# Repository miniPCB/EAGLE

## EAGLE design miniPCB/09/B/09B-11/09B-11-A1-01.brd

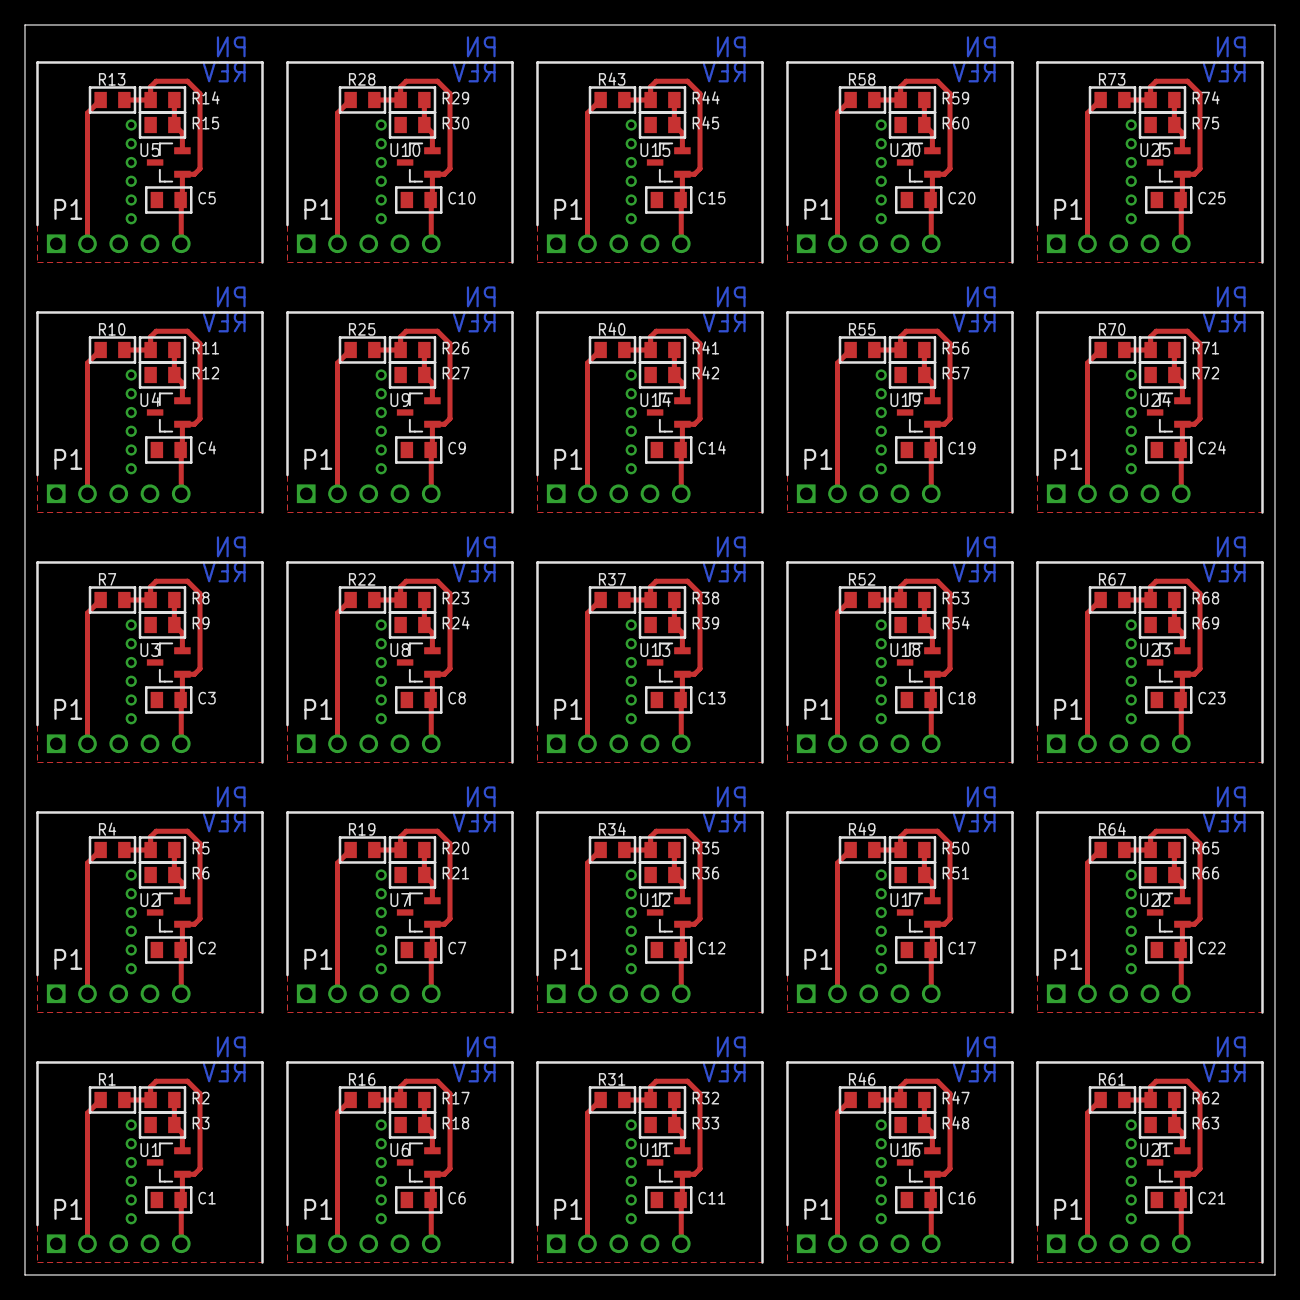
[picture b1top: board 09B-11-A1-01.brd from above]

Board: 2 copper layers, 100.0 x 100.0 mm, 175 parts (0 on the bottom side), 100 nets.

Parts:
C1, C2, C3, C4, C5, C6, C7, C8, C9, C10, C11, C12, C13, C14, C15, C16, C17, C18, C19, C20, C21, C22, C23, C24, C25: C0805
P1, P2, P3, P4, P5, P6, P7, P8, P9, P10, P11, P12, P13, P14, P15, P16, P17, P18, P19, P20, P21, P22, P23, P24, P25: PINS_1X5
PCB1, PCB2, PCB3, PCB4, PCB5, PCB6, PCB7, PCB8, PCB9, PCB10, PCB11, PCB12, PCB13, PCB14, PCB15, PCB16, PCB17, PCB18, PCB19, PCB20, PCB21, PCB22, PCB23, PCB24, PCB25: PCB20-20
R1, R2, R3, R4, R5, R6, R7, R8, R9, R10, R11, R12, R13, R14, R15, R16, R17, R18, R19, R20, R21, R22, R23, R24, R25, R26, R27, R28, R29, R30, R31, R32, R33, R34, R35, R36, R37, R38, R39, R40, R41, R42, R43, R44, R45, R46, R47, R48, R49, R50, R51, R52, R53, R54, R55, R56, R57, R58, R59, R60, R61, R62, R63, R64, R65, R66, R67, R68, R69, R70, R71, R72, R73, R74, R75: R0805
U1, U2, U3, U4, U5, U6, U7, U8, U9, U10, U11, U12, U13, U14, U15, U16, U17, U18, U19, U20, U21, U22, U23, U24, U25: TL432BQDBZRQ1; SOT95P237X112-3N

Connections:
GND20: C1.2ASDF, P1.1, R3.1, U1.3
GND21: C2.2ASDF, P2.1, R6.1, U2.3
GND22: C3.2ASDF, P3.1, R9.1, U3.3
GND23: C4.2ASDF, P4.1, R12.1, U4.3
GND24: C5.2ASDF, P5.1, R15.1, U5.3
GND25: C6.2ASDF, P6.1, R18.1, U6.3
GND26: C7.2ASDF, P7.1, R21.1, U7.3
GND27: C8.2ASDF, P8.1, R24.1, U8.3
GND28: C9.2ASDF, P9.1, R27.1, U9.3
GND29: C10.2ASDF, P10.1, R30.1, U10.3
GND30: C11.2ASDF, P11.1, R33.1, U11.3
GND31: C12.2ASDF, P12.1, R36.1, U12.3
GND32: C13.2ASDF, P13.1, R39.1, U13.3
GND33: C14.2ASDF, P14.1, R42.1, U14.3
GND34: C15.2ASDF, P15.1, R45.1, U15.3
GND35: C16.2ASDF, P16.1, R48.1, U16.3
GND36: C17.2ASDF, P17.1, R51.1, U17.3
GND37: C18.2ASDF, P18.1, R54.1, U18.3
GND38: C19.2ASDF, P19.1, R57.1, U19.3
GND39: C20.2ASDF, P20.1, R60.1, U20.3
GND40: C21.2ASDF, P21.1, R63.1, U21.3
GND41: C22.2ASDF, P22.1, R66.1, U22.3
GND42: C23.2ASDF, P23.1, R69.1, U23.3
GND43: C24.2ASDF, P24.1, R72.1, U24.3
GND44: C25.2ASDF, P25.1, R75.1, U25.3
unnamed: C1.1ASD, P1.5, R1.1, R2.2, U1.1
unnamed: R2.1, R3.2, U1.2
unnamed: C2.1ASD, P2.5, R4.1, R5.2, U2.1
unnamed: R5.1, R6.2, U2.2
unnamed: C3.1ASD, P3.5, R7.1, R8.2, U3.1
unnamed: R8.1, R9.2, U3.2
unnamed: C4.1ASD, P4.5, R10.1, R11.2, U4.1
unnamed: R11.1, R12.2, U4.2
unnamed: C5.1ASD, P5.5, R13.1, R14.2, U5.1
unnamed: R14.1, R15.2, U5.2
unnamed: C6.1ASD, P6.5, R16.1, R17.2, U6.1
unnamed: R17.1, R18.2, U6.2
unnamed: C7.1ASD, P7.5, R19.1, R20.2, U7.1
unnamed: R20.1, R21.2, U7.2
unnamed: C8.1ASD, P8.5, R22.1, R23.2, U8.1
unnamed: R23.1, R24.2, U8.2
unnamed: C9.1ASD, P9.5, R25.1, R26.2, U9.1
unnamed: R26.1, R27.2, U9.2
unnamed: C10.1ASD, P10.5, R28.1, R29.2, U10.1
unnamed: R29.1, R30.2, U10.2
unnamed: C11.1ASD, P11.5, R31.1, R32.2, U11.1
unnamed: R32.1, R33.2, U11.2
unnamed: C12.1ASD, P12.5, R34.1, R35.2, U12.1
unnamed: R35.1, R36.2, U12.2
unnamed: C13.1ASD, P13.5, R37.1, R38.2, U13.1
unnamed: R38.1, R39.2, U13.2
unnamed: C14.1ASD, P14.5, R40.1, R41.2, U14.1
unnamed: R41.1, R42.2, U14.2
unnamed: C15.1ASD, P15.5, R43.1, R44.2, U15.1
unnamed: R44.1, R45.2, U15.2
unnamed: C16.1ASD, P16.5, R46.1, R47.2, U16.1
unnamed: R47.1, R48.2, U16.2
unnamed: C17.1ASD, P17.5, R49.1, R50.2, U17.1
unnamed: R50.1, R51.2, U17.2
unnamed: C18.1ASD, P18.5, R52.1, R53.2, U18.1
unnamed: R53.1, R54.2, U18.2
unnamed: C19.1ASD, P19.5, R55.1, R56.2, U19.1
unnamed: R56.1, R57.2, U19.2
unnamed: C20.1ASD, P20.5, R58.1, R59.2, U20.1
unnamed: R59.1, R60.2, U20.2
unnamed: C21.1ASD, P21.5, R61.1, R62.2, U21.1
unnamed: R62.1, R63.2, U21.2
unnamed: C22.1ASD, P22.5, R64.1, R65.2, U22.1
unnamed: R65.1, R66.2, U22.2
unnamed: C23.1ASD, P23.5, R67.1, R68.2, U23.1
unnamed: R68.1, R69.2, U23.2
unnamed: C24.1ASD, P24.5, R70.1, R71.2, U24.1
unnamed: R71.1, R72.2, U24.2
unnamed: C25.1ASD, P25.5, R73.1, R74.2, U25.1
unnamed: R74.1, R75.2, U25.2
V+: P1.2, R1.2
V+1: P2.2, R4.2
V+2: P3.2, R7.2
V+3: P4.2, R10.2
V+4: P5.2, R13.2
V+5: P6.2, R16.2
V+6: P7.2, R19.2
V+7: P8.2, R22.2
V+8: P9.2, R25.2
V+9: P10.2, R28.2
V+10: P11.2, R31.2
V+11: P12.2, R34.2
V+12: P13.2, R37.2
V+13: P14.2, R40.2
V+14: P15.2, R43.2
V+15: P16.2, R46.2
V+16: P17.2, R49.2
V+17: P18.2, R52.2
V+18: P19.2, R55.2
V+19: P20.2, R58.2
V+20: P21.2, R61.2
V+21: P22.2, R64.2
V+22: P23.2, R67.2
V+23: P24.2, R70.2
V+24: P25.2, R73.2

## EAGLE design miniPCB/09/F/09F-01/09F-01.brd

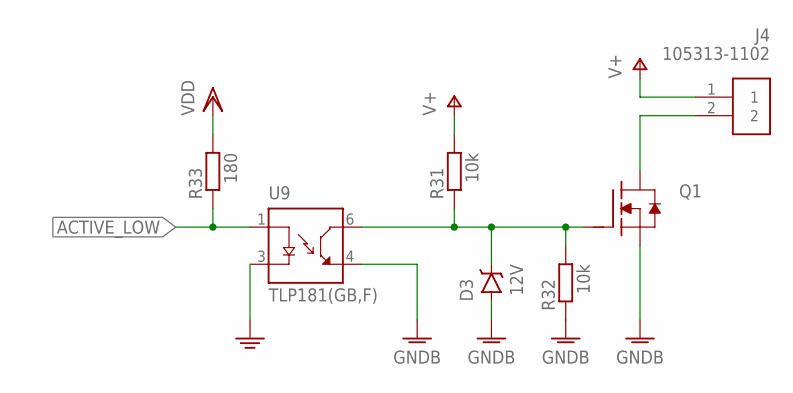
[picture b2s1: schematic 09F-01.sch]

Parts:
D3: 12V; SOT23
J4: 105313-1102; PINS_2-NANOFIT-H
Q1: MOSFET-NDPAK; DPACK
R31, R32: 10k; R0805
R33: 180; R0805
U9: TLP181(GB,F); SOIC254P700X280-4N

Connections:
ACTIVE_LOW: R33.1, U9.1 (A)
GND: U9.3 (C)
GNDB: D3.1 (A), Q1.3 (S), R32.1, U9.4 (ET)
unnamed: D3.3 (C), Q1.1 (G), R31.1, R32.2, U9.6 (CT)
unnamed: J4.2, Q1.4 (D)
V+: J4.1, R31.2
VDD: R33.2

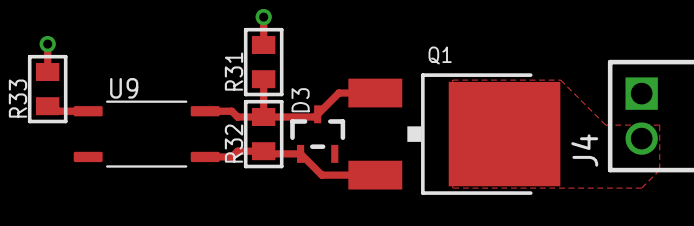
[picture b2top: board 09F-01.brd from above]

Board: 2 copper layers, 7 parts (0 on the bottom side), 5 nets.

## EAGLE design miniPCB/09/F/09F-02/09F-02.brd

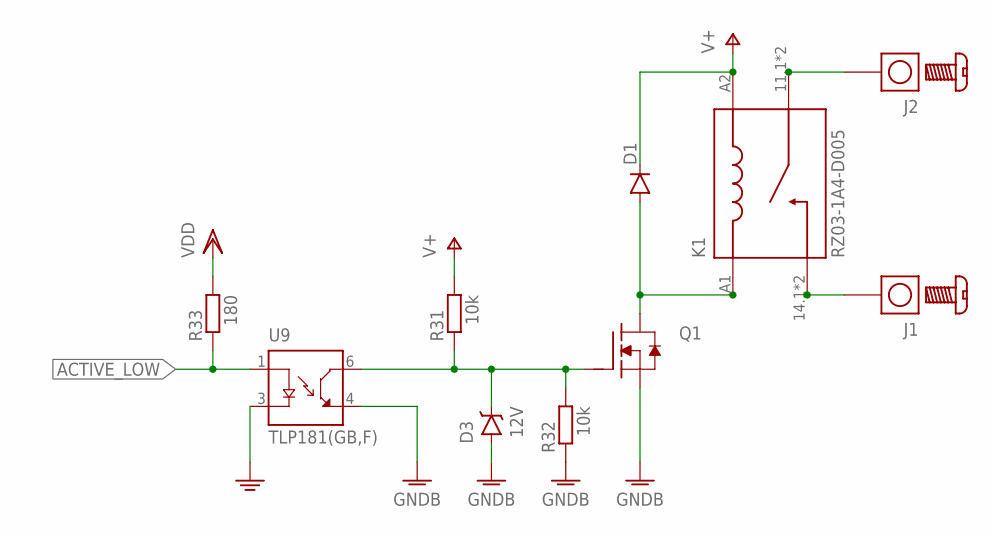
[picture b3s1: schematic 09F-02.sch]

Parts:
D1: DIODE-SOD323-W; SOD323-W
D3: 12V; SOT23
J1, J2: SCREW-TERMINAL; SCREW-TERMINAL-M3
K1: RZ03-1A4-D005; RELAY_RZ03-1A4-D005
Q1: MOSFET-NSOT23; SOT23
R31, R32: 10k; R0805
R33: 180; R0805
U9: TLP181(GB,F); SOIC254P700X280-4N

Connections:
ACTIVE_LOW: R33.1, U9.1 (A)
GND: U9.3 (C)
GNDB: D3.1 (A), Q1.2 (S), R32.1, U9.4 (ET)
unnamed: J2.1, J2.2, J2.3, J2.4, K1.11.1 (11), K1.11.2 (11)
unnamed: J1.1, J1.2, J1.3, J1.4, K1.14.1 (14), K1.14.2 (14)
unnamed: D3.3 (C), Q1.1 (G), R31.1, R32.2, U9.6 (CT)
unnamed: D1.A, K1.A1, Q1.3 (D)
V+: D1.C, K1.A2, R31.2
VDD: R33.2

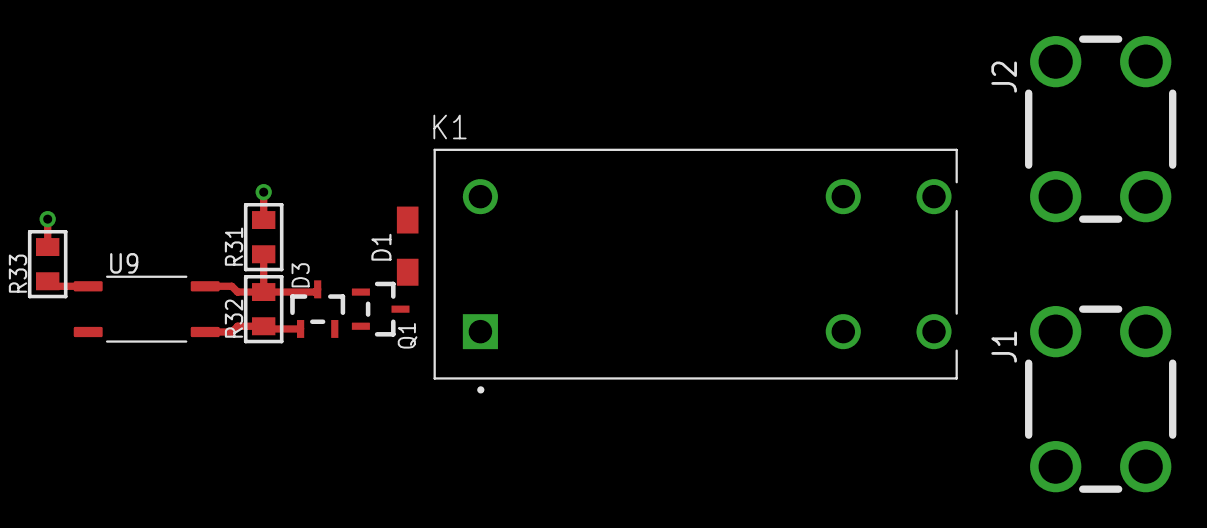
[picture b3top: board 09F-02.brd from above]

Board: 2 copper layers, 10 parts (0 on the bottom side), 7 nets.

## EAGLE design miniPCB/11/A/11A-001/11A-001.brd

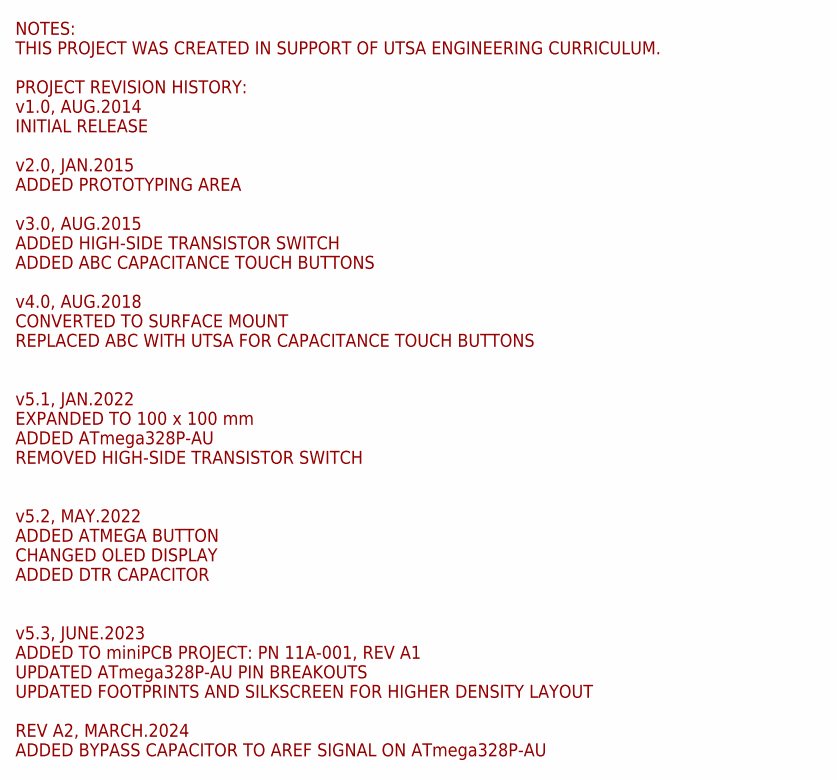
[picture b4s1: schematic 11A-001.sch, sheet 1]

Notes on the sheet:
NOTES: THIS PROJECT WAS CREATED IN SUPPORT OF UTSA ENGINEERING CURRICULUM. PROJECT REVISION HISTORY: v1.0, AUG.2014 INITIAL RELEASE v2.0, JAN.2015 ADDED PROTOTYPING AREA v3.0, AUG.2015 ADDED HIGH-SIDE TRANSISTOR SWITCH ADDED ABC CAPACITANCE TOUCH BUTTONS v4.0, AUG.2018 CONVERTED TO SURFACE MOUNT RE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

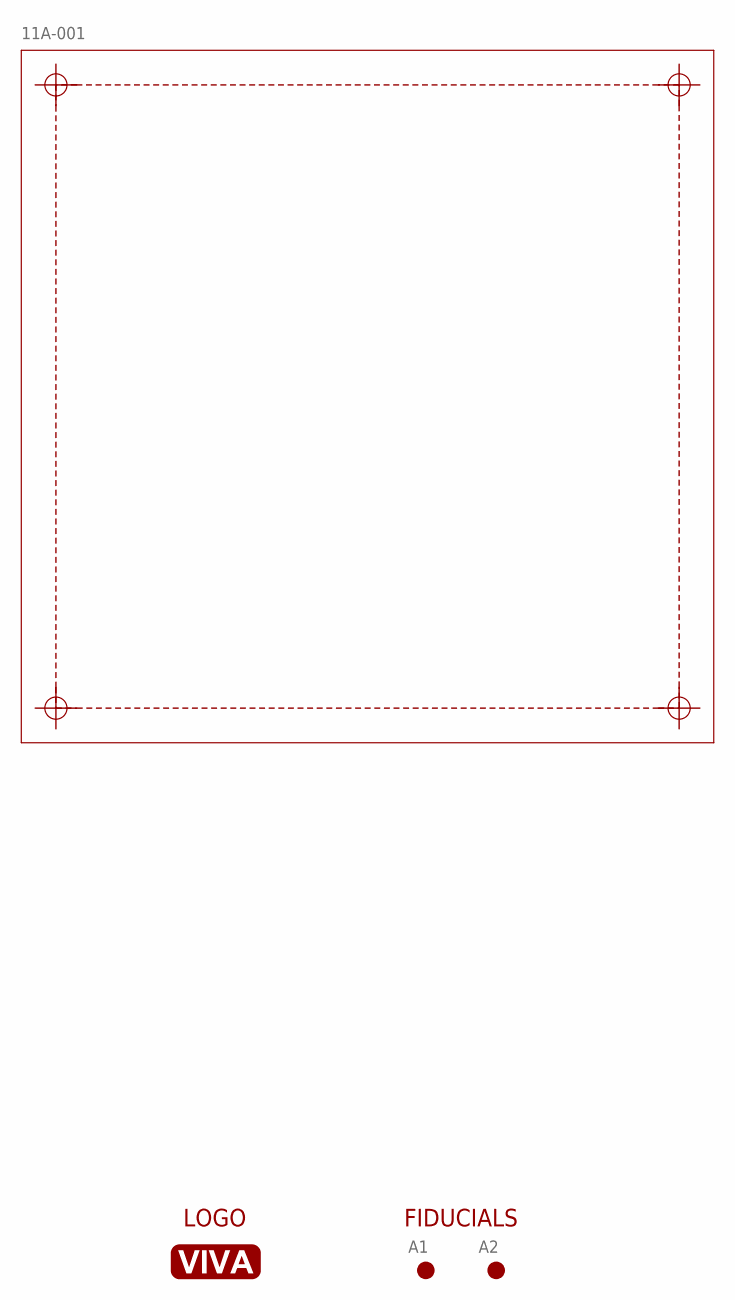
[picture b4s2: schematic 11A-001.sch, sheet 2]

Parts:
-: 11A-001; PCB_100X100
A1, A2: FIDUCIAL
U$2: VIVA_LOGO

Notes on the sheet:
FIDUCIALS
LOGO

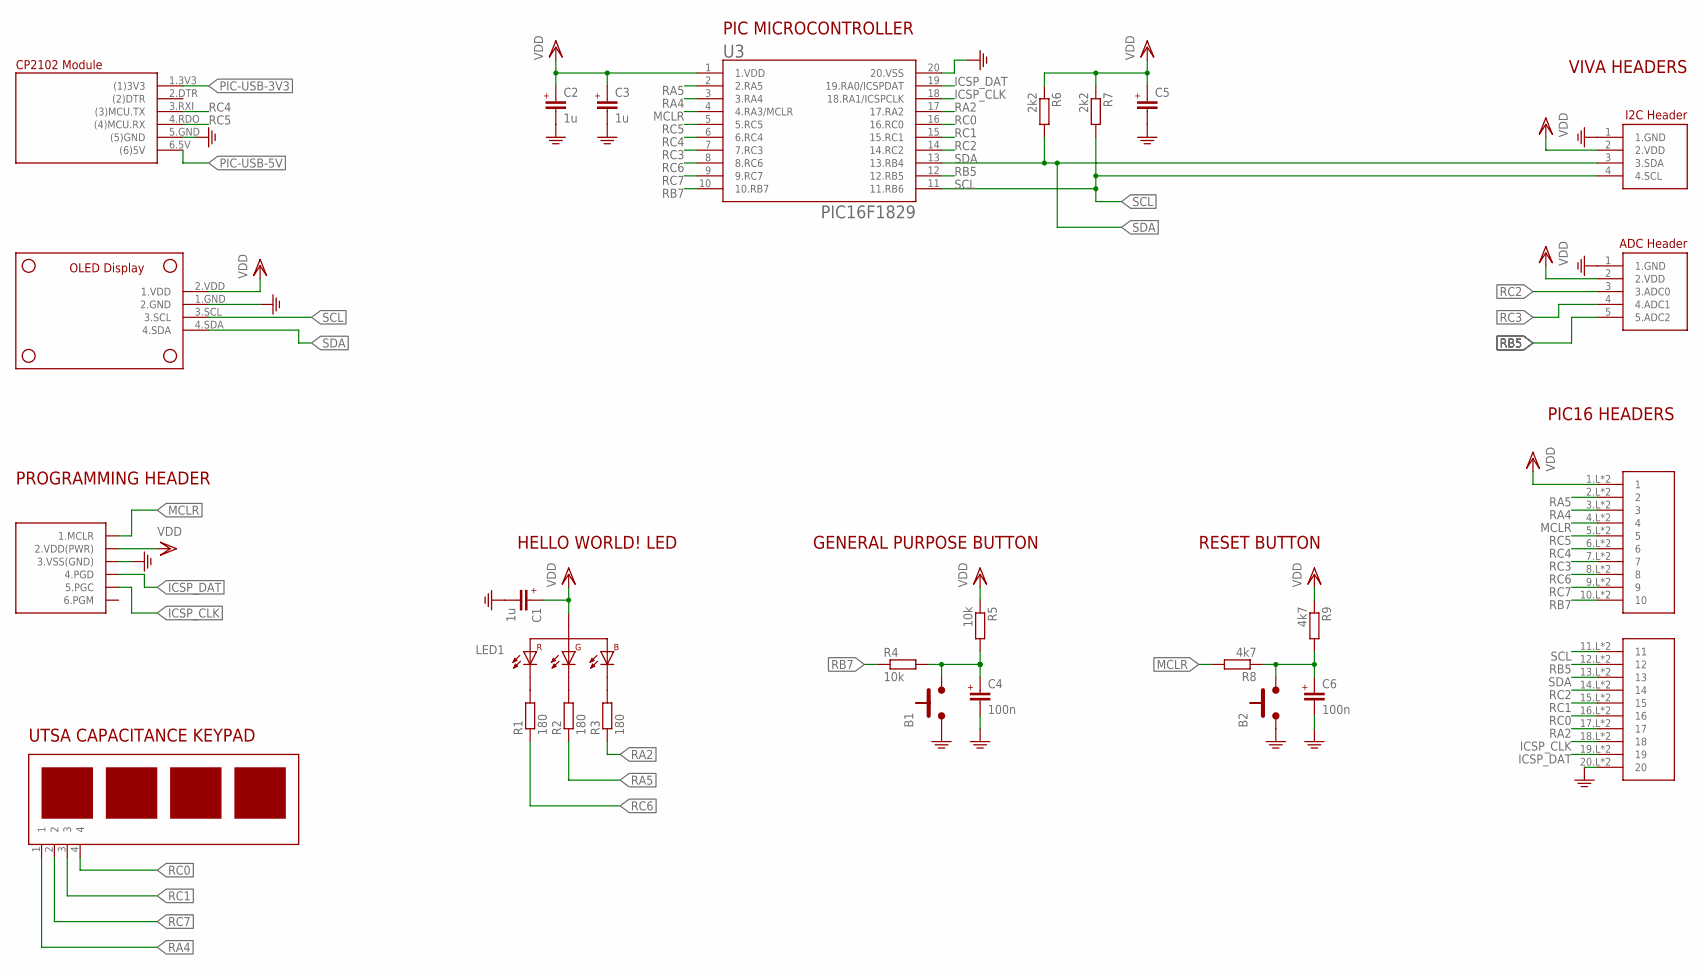
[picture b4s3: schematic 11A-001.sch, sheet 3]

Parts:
$3_73_$: VIVA_OLEDGND; VIVA_OLED-I2C-ALT
B1, B2: PUSHBUTTON6X6MM; 6X6MM
C1, C2, C3: 1u; C0805
C4, C6: 100n; C0805
C5: C0805
J1: PICKIT3
J2: VIVA-HEADER-ADC-PIC16
LED1: LED_RGBLTST-C19FD1WT; 0805_RGB
R1, R2, R3: 180; R0805
R4, R5: 10k; R0805
R6, R7: 2k2; R0805
R8, R9: 4k7; R0805
U1: VIVA_UTSA-KEYPADV5; VIVA_UTSA-KEYPAD-V5
U2: VIVA_USB-TTL; VIVA_USB_TTL_SUBTEXT
U3: PIC16F1829; SOP20-NEW
U4: VIVA-HEADER-I2C-RA
U5: VIVA_PIC16BOARD; VIVA_PIC16

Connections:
B1-CAP: B1.3.B (2), B1.4.B (2), C4.1 (+), R4.2, R5.2
GND: $3_73_$.1.GND (2.GND), B1.1.A (1), B1.2.A (1), B2.1.A (1), B2.2.A (1), C1.2 (-), C2.2 (-), C3.2 (-), C4.2 (-), C5.2 (-), C6.2 (-), J1.3 (3.VSS(GND)), J2.1 (1.GND), U2.5.GND ((5)GND), U3.20 (20.VSS), U4.1 (1.GND), U5.20.L (20), U5.20.R (20); also elsewhere on the board
ICSP_CLK: J1.5 (5.PGC), U3.18 (18.RA1/ICSPCLK), U5.18.L (18), U5.18.R (18)
ICSP_DAT: J1.4 (4.PGD), U3.19 (19.RA0/ICSPDAT), U5.19.L (19), U5.19.R (19)
MCLR: J1.1 (1.MCLR), R8.2, U3.4 (4.RA3/MCLR), U5.4.L (4), U5.4.R (4)
MCLR_CAP: B2.3.B (2), B2.4.B (2), C6.1 (+), R8.1, R9.2
unnamed: LED1.2 (1.R-), R1.2
unnamed: LED1.3 (2.G-), R2.2
unnamed: LED1.1 (4.B-), R3.2
PIC-USB-3V3: U2.1.3V3 ((1)3V3); also elsewhere on the board
PIC-USB-5V: U2.6.5V ((6)5V); also elsewhere on the board
RA2: R3.1, U3.17 (17.RA2), U5.17.L (17), U5.17.R (17)
RA4: U1.1, U3.3 (3.RA4), U5.3.L (3), U5.3.R (3)
RA5: R2.1, U3.2 (2.RA5), U5.2.L (2), U5.2.R (2)
RB5: J2.5 (5.ADC2), U3.12 (12.RB5), U5.12.L (12), U5.12.R (12)
RB7: R4.1, U3.10 (10.RB7), U5.10.L (10), U5.10.R (10)
RC0: U1.4, U3.16 (16.RC0), U5.16.L (16), U5.16.R (16)
RC1: U1.3, U3.15 (15.RC1), U5.15.L (15), U5.15.R (15)
RC2: J2.3 (3.ADC0), U3.14 (14.RC2), U5.14.L (14), U5.14.R (14)
RC3: J2.4 (4.ADC1), U3.7 (7.RC3), U5.7.L (7), U5.7.R (7)
RC4: U2.3.RXI ((3)MCU.TX), U3.6 (6.RC4), U5.6.L (6), U5.6.R (6)
RC5: U2.4.RDO ((4)MCU.RX), U3.5 (5.RC5), U5.5.L (5), U5.5.R (5)
RC6: R1.1, U3.8 (8.RC6), U5.8.L (8), U5.8.R (8)
RC7: U1.2, U3.9 (9.RC7), U5.9.L (9), U5.9.R (9)
SCL: $3_73_$.3.SCL, R7.2, U3.11 (11.RB6), U4.4 (4.SCL), U5.11.L (11), U5.11.R (11); also elsewhere on the board
SDA: $3_73_$.4.SDA, R6.2, U3.13 (13.RB4), U4.3 (3.SDA), U5.13.L (13), U5.13.R (13); also elsewhere on the board
VDD: $3_73_$.2.VDD (1.VDD), C1.1 (+), C2.1 (+), C3.1 (+), C5.1 (+), J1.2 (2.VDD(PWR)), J2.2 (2.VDD), LED1.4 (3.+), R5.1, R6.1, R7.1, R9.1, U3.1 (1.VDD), U4.2 (2.VDD), U5.1.L (1), U5.1.R (1); also elsewhere on the board

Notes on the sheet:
GENERAL PURPOSE BUTTON
HELLO WORLD! LED
PIC MICROCONTROLLER
UTSA CAPACITANCE KEYPAD
RESET BUTTON
PROGRAMMING HEADER
PIC16 HEADERS
VIVA HEADERS

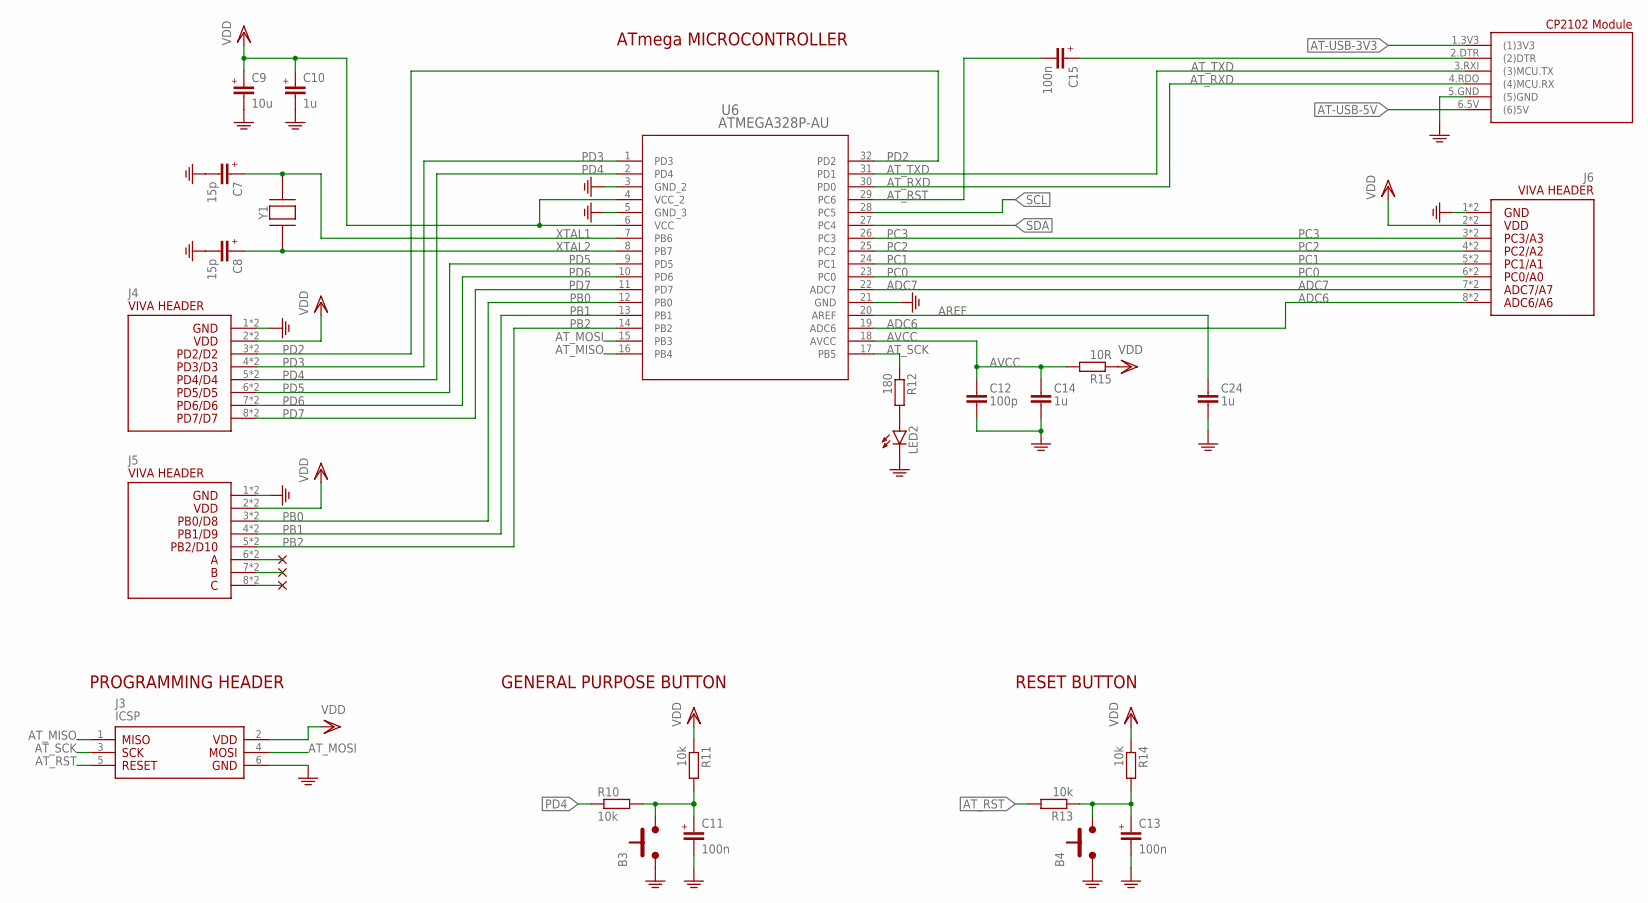
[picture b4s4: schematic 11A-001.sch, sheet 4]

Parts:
B3, B4: PUSHBUTTON6X6MM; 6X6MM
C7, C8: 15p; C0603
C9: 10u; C0805
C10, C14, C24: 1u; C0805
C11, C13, C15: 100n; C0805
C12: 100p; C0805
J3: ICSP; PINS_6-2X3_AT
J4, J5, J6: VIVA-HEADER-ADC-8P
LED2: LEDSML0805; SML0805
R10, R11, R13, R14: 10k; R0805
R12: 180; R0805
R15: 10R; R0805
U6: ATMEGA328P-AU; 32A_ATM
U7: VIVA_USB-TTL; VIVA_USB_TTL_SUBTEXT
Y1: CRYSTAL-3225_4P; TXC7M2

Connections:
ADC6: J6.8 (8.ADC5), J6.9 (8.ADC5), U6.19 (ADC6)
ADC7: J6.7 (7.ADC4), J6.10 (7.ADC4), U6.22 (ADC7)
AREF: C24.1, U6.20 (AREF)
AT-USB-3V3: U7.1.3V3 ((1)3V3); also elsewhere on the board
AT-USB-5V: U7.6.5V ((6)5V); also elsewhere on the board
AT_DTR_CAP: C15.1 (+), U7.2.DTR ((2)DTR)
AT_MISO: J3.1, U6.16 (PB4)
AT_MOSI: J3.4, U6.15 (PB3)
AT_RST: C15.2 (-), J3.5, R13.2, U6.29 (PC6)
AT_RST_CAP: B4.3.B (2), B4.4.B (2), C13.1 (+), R13.1, R14.2
AT_RXD: U6.30 (PD0), U7.4.RDO ((4)MCU.RX)
AT_SCK: J3.3, R12.1, U6.17 (PB5)
AT_TXD: U6.31 (PD1), U7.3.RXI ((3)MCU.TX)
AVCC: C12.1, C14.1, R15.2, U6.18 (AVCC)
GND: B3.1.A (1), B3.2.A (1), B4.1.A (1), B4.2.A (1), C7.1 (-), C8.1 (-), C9.2 (-), C10.2 (-), C11.2 (-), C12.2, C13.2 (-), C14.2, C24.2, J3.6, J4.1 (1.GND), J4.16 (1.GND), J5.1 (1.GND), J5.16 (1.GND), J6.1 (1.GND), J6.16 (1.GND), LED2.C, U6.3 (GND_2), U6.5 (GND_3), U6.21 (GND), U7.5.GND ((5)GND); also elsewhere on the board
unnamed: J5.6 (6.ADC3), J5.11 (6.ADC3)
unnamed: J5.7 (7.ADC4), J5.10 (7.ADC4)
unnamed: J5.8 (8.ADC5), J5.9 (8.ADC5)
unnamed: LED2.A, R12.2
PB0: J5.3 (3.ADC0), J5.14 (3.ADC0), U6.12 (PB0)
PB1: J5.4 (4.ADC1), J5.13 (4.ADC1), U6.13 (PB1)
PB2: J5.5 (5.ADC2), J5.12 (5.ADC2), U6.14 (PB2)
PC0: J6.6 (6.ADC3), J6.11 (6.ADC3), U6.23 (PC0)
PC1: J6.5 (5.ADC2), J6.12 (5.ADC2), U6.24 (PC1)
PC2: J6.4 (4.ADC1), J6.13 (4.ADC1), U6.25 (PC2)
PC3: J6.3 (3.ADC0), J6.14 (3.ADC0), U6.26 (PC3)
PD2: J4.3 (3.ADC0), J4.14 (3.ADC0), U6.32 (PD2)
PD3: J4.4 (4.ADC1), J4.13 (4.ADC1), U6.1 (PD3)
PD4: J4.5 (5.ADC2), J4.12 (5.ADC2), R10.1, U6.2 (PD4)
PD4-CAP: B3.3.B (2), B3.4.B (2), C11.1 (+), R10.2, R11.2
PD5: J4.6 (6.ADC3), J4.11 (6.ADC3), U6.9 (PD5)
PD6: J4.7 (7.ADC4), J4.10 (7.ADC4), U6.10 (PD6)
PD7: J4.8 (8.ADC5), J4.9 (8.ADC5), U6.11 (PD7)
SCL: U6.28 (PC5); also elsewhere on the board
SDA: U6.27 (PC4); also elsewhere on the board
VDD: C9.1 (+), C10.1 (+), J3.2, J4.2 (2.VDD), J4.15 (2.VDD), J5.2 (2.VDD), J5.15 (2.VDD), J6.2 (2.VDD), J6.15 (2.VDD), R11.1, R14.1, R15.1, U6.4 (VCC_2), U6.6 (VCC); also elsewhere on the board
XTAL1: C7.2 (+), U6.7 (PB6), Y1.3 (2)
XTAL2: C8.2 (+), U6.8 (PB7), Y1.1

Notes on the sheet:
RESET BUTTON
PROGRAMMING HEADER
GENERAL PURPOSE BUTTON
ATmega MICROCONTROLLER

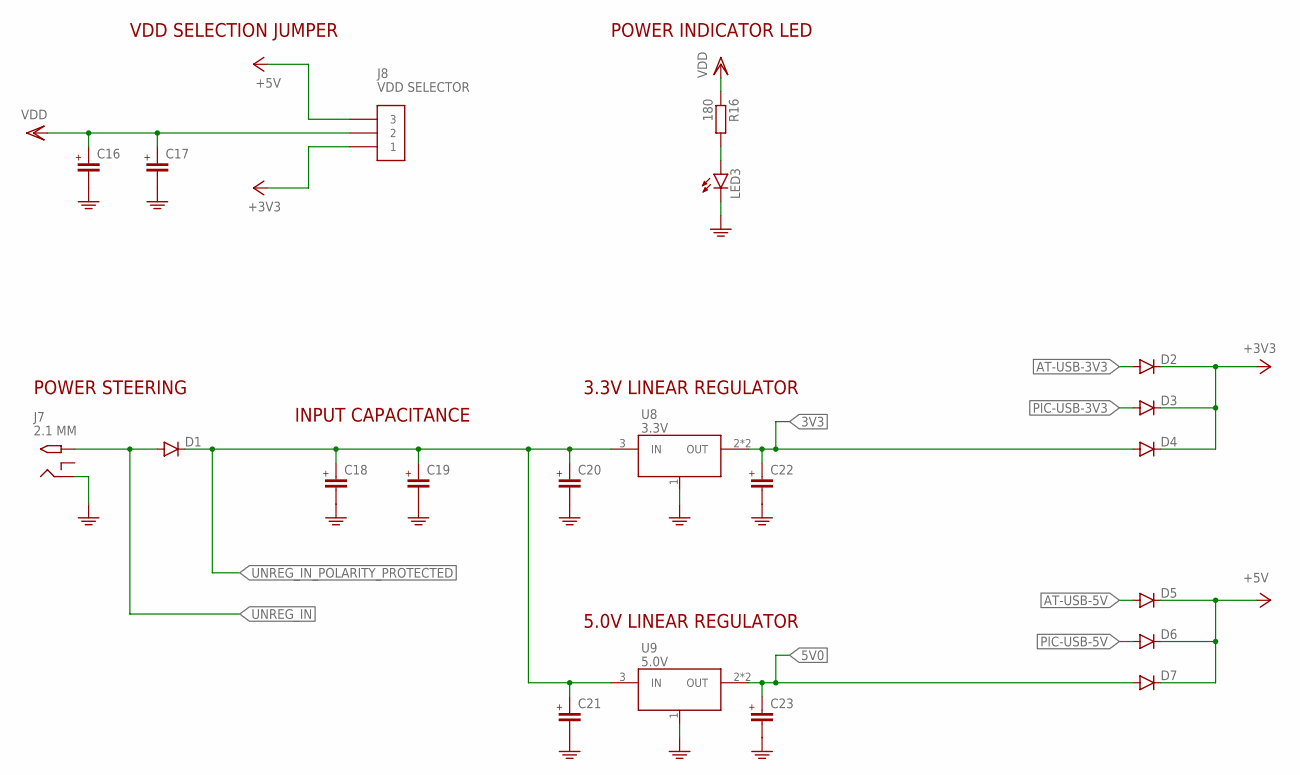
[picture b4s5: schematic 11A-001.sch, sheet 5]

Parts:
C16, C17, C18, C19, C20, C21, C22, C23: C0805
D1, D2, D3, D4, D5, D6, D7: DIODE-DO214AC; DO214AC
J7: 2.1 MM; PJ-102A
J8: VDD SELECTOR; PINS_3
LED3: LEDSML0805; SML0805
R16: 180; R0805
U8: 3.3V; SOT223
U9: 5.0V; SOT223

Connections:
3V3: C22.1 (+), D4.A, U8.2 (OUT), U8.4.TAB (OUT)
5V0: C23.1 (+), D7.A, U9.2 (OUT), U9.4.TAB (OUT)
+3V3: D2.C, D3.C, D4.C, J8.1
+5V: D5.C, D6.C, D7.C, J8.3
AT-USB-3V3: D2.A; also elsewhere on the board
AT-USB-5V: D5.A; also elsewhere on the board
GND: C16.2 (-), C17.2 (-), C18.2 (-), C19.2 (-), C20.2 (-), C21.2 (-), C22.2 (-), C23.2 (-), J7.RING, LED3.C, U8.1 (GND), U9.1 (GND); also elsewhere on the board
LED_POWER: LED3.A, R16.2
PIC-USB-3V3: D3.A; also elsewhere on the board
PIC-USB-5V: D6.A; also elsewhere on the board
UNREG_IN: D1.A, J7.TIP
UNREG_IN_POLARITY_PROTECTED: C18.1 (+), C19.1 (+), C20.1 (+), C21.1 (+), D1.C, U8.3 (IN), U9.3 (IN)
VDD: C16.1 (+), C17.1 (+), J8.2, R16.1; also elsewhere on the board

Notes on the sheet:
VDD SELECTION JUMPER
POWER INDICATOR LED
3.3V LINEAR REGULATOR
5.0V LINEAR REGULATOR
POWER STEERING
INPUT CAPACITANCE

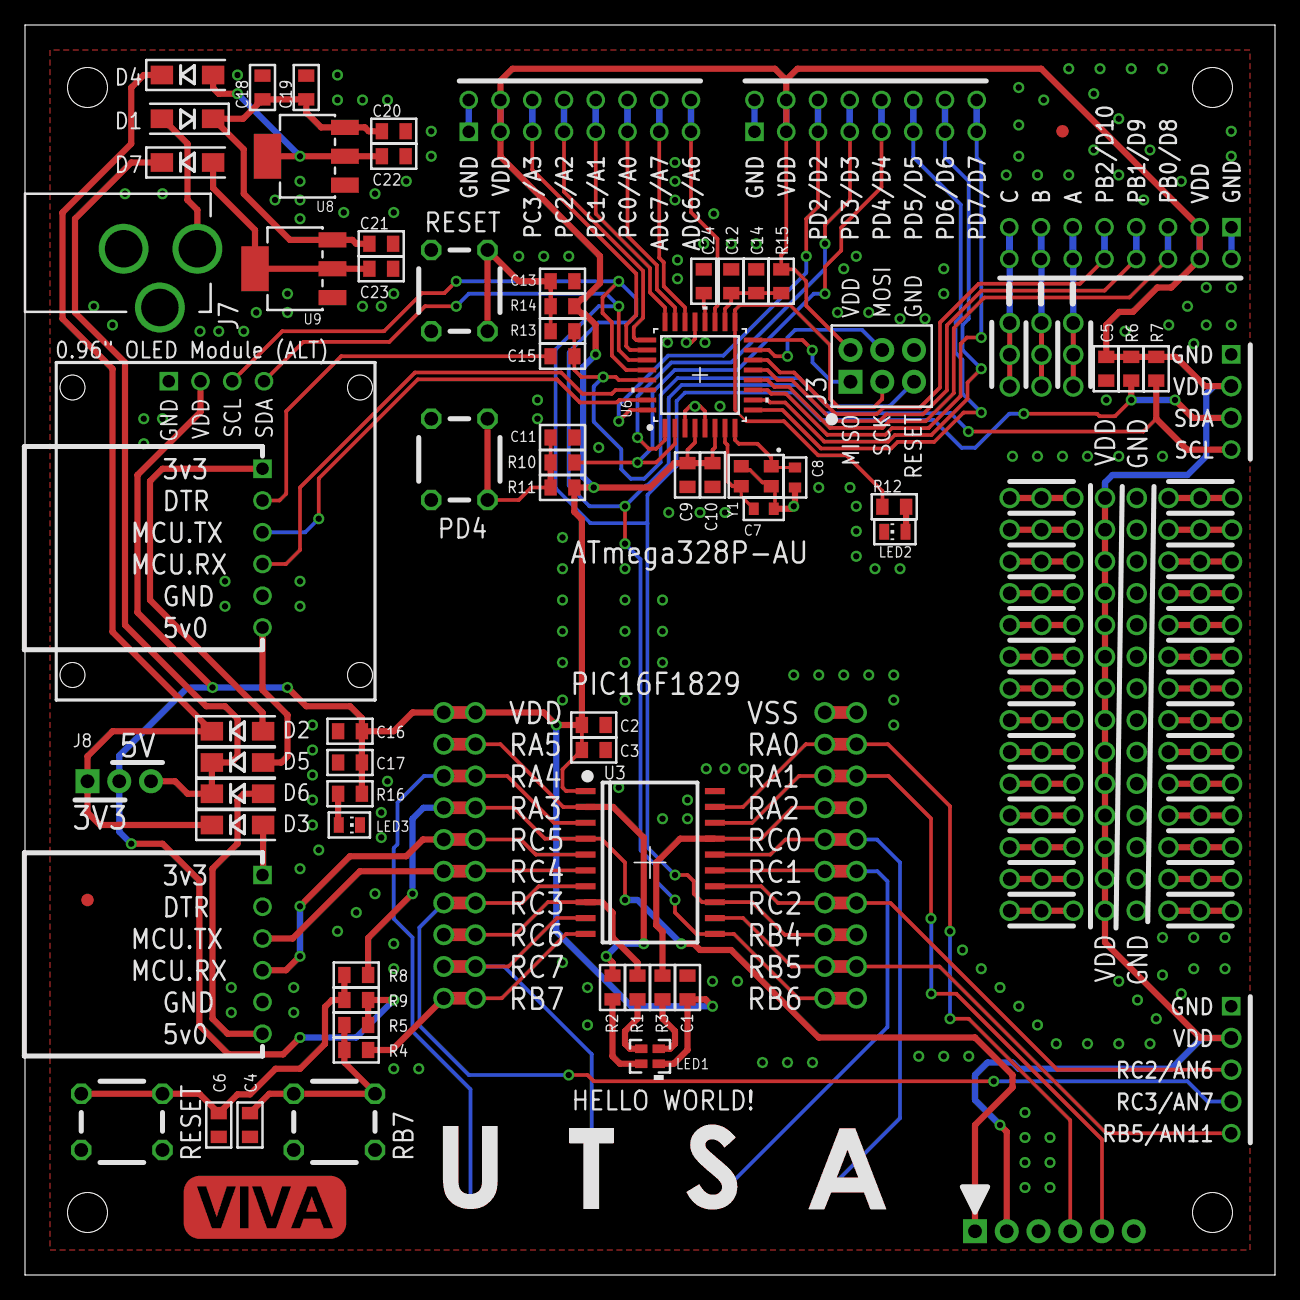
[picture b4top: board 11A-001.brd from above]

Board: 2 copper layers, 100.0 x 100.0 mm, 78 parts (0 on the bottom side), 68 nets.

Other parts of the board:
U$1: MINIPCB_PANEL_IMAGEFRAME

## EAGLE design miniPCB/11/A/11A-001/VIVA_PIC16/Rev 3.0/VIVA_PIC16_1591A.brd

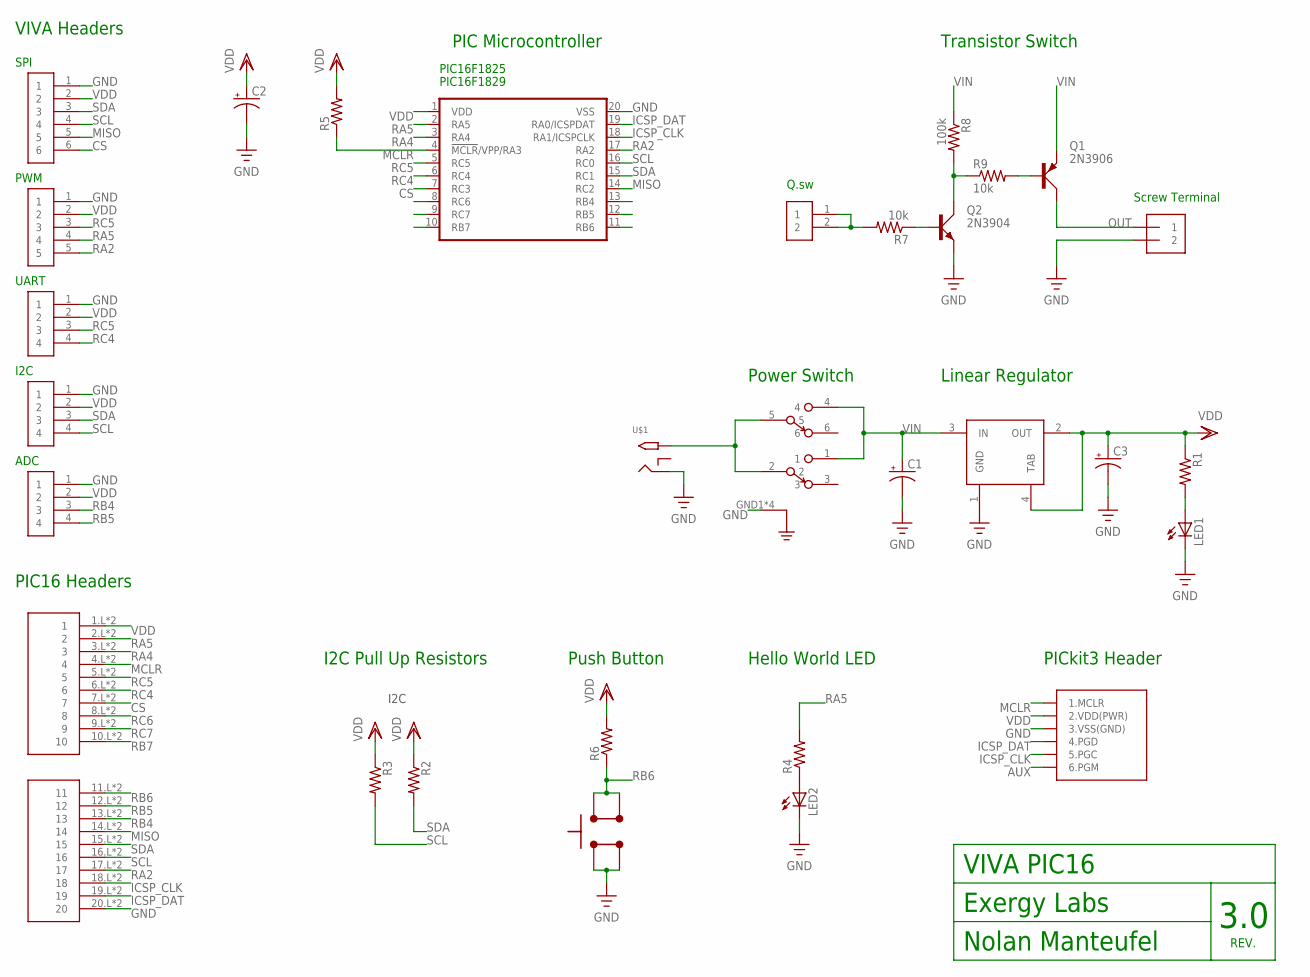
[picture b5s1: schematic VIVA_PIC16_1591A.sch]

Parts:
C1, C2, C3: CPOL-USE2.5-6; E2,5-6
J1: 1X2-3.5MM
LED1, LED2: LED5MM
PIC16F1823: PIC16F1829; DIL20
Q1: 2N3906; TO92-EBC-OVAL
Q2: 2N3904; TO92-EBC-OVAL
R1, R2, R3, R4, R5, R6: R-US_0204/5; 0204/5
R7, R9: 10k; 0204/5
R8: 100k; 0204/5
U1: REGULATOR_SCHSOT223; SOT223
U$1: 2.1MMJACKTHM; PJ-102A
U$3: SWITCH_OS202013; OS202013MT5QN1
U$4: PUSHBUTTON_THD; PUSHBUTTON_1301_9303
U$5: PINS_5
U$6, U$7, U$8: PINS_4
U$9: PINS_6
U$10: PINS_2
U$11: PICKIT3
U$12: VIVA_PIC16

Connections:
AUX: U$11.6 (6.PGM)
BAT: U$1.TIP, U$3.2, U$3.5
CS: PIC16F1823.7 (RC3), U$9.6, U$12.7.L (7), U$12.7.R (7)
GND: C1.-, C2.-, C3.-, J1.2, LED1.K (C), LED2.K (C), PIC16F1823.20 (VSS), Q2.E, U1.1 (GND), U$1.RING, U$3.GND1 (GND), U$3.GND2 (GND), U$3.GND3 (GND), U$3.GND4 (GND), U$4.1, U$4.2, U$5.1, U$6.1, U$7.1, U$8.1, U$9.1, U$11.3 (3.VSS(GND)), U$12.20.L (20), U$12.20.R (20)
ICSP_CLK: PIC16F1823.18 (RA1/ICSPCLK), U$11.5 (5.PGC), U$12.18.L (18), U$12.18.R (18)
ICSP_DAT: PIC16F1823.19 (RA0/ICSPDAT), U$11.4 (4.PGD), U$12.19.L (19), U$12.19.R (19)
MCLR: PIC16F1823.4 (!MCLR!/VPP/RA3), R5.1, U$11.1 (1.MCLR), U$12.4.L (4), U$12.4.R (4)
MISO: PIC16F1823.14 (RC2), U$9.5, U$12.14.L (14), U$12.14.R (14)
unnamed: Q2.B, R7.1
unnamed: Q2.C, R8.2, R9.1
unnamed: Q1.B, R9.2
unnamed: R7.2, U$10.1, U$10.2
unnamed: LED1.A, R1.2
unnamed: LED2.A, R4.1
OUT: J1.1, Q1.C
RA2: PIC16F1823.17 (RA2), U$5.5, U$12.17.L (17), U$12.17.R (17)
RA4: PIC16F1823.3 (RA4), U$12.3.L (3), U$12.3.R (3)
RA5: PIC16F1823.2 (RA5), R4.2, U$5.4, U$12.2.L (2), U$12.2.R (2)
RB4: PIC16F1823.13 (RB4), U$8.3, U$12.13.L (13), U$12.13.R (13)
RB5: PIC16F1823.12 (RB5), U$8.4, U$12.12.L (12), U$12.12.R (12)
RB6: PIC16F1823.11 (RB6), R6.1, U$4.3, U$4.4, U$12.11.L (11), U$12.11.R (11)
RB7: PIC16F1823.10 (RB7), U$12.10.L (10), U$12.10.R (10)
RC4: PIC16F1823.6 (RC4), U$6.4, U$12.6.L (6), U$12.6.R (6)
RC5: PIC16F1823.5 (RC5), U$5.3, U$6.3, U$12.5.L (5), U$12.5.R (5)
RC6: PIC16F1823.8 (RC6), U$12.8.L (8), U$12.8.R (8)
RC7: PIC16F1823.9 (RC7), U$12.9.L (9), U$12.9.R (9)
SCL: PIC16F1823.16 (RC0), R3.2, U$7.4, U$9.4, U$12.16.L (16), U$12.16.R (16)
SDA: PIC16F1823.15 (RC1), R2.2, U$7.3, U$9.3, U$12.15.L (15), U$12.15.R (15)
VDD: C2.+, C3.+, PIC16F1823.1 (VDD), R1.1, R2.1, R3.1, R5.2, R6.2, U1.2 (OUT), U1.4 (TAB), U$5.2, U$6.2, U$7.2, U$8.2, U$9.2, U$11.2 (2.VDD(PWR)), U$12.1.L (1), U$12.1.R (1)
VIN: C1.+, Q1.E, R8.1, U1.3 (IN), U$3.1, U$3.4

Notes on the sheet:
REV.
3.0
VIVA PIC16
Exergy Labs
Nolan Manteufel
I2C
PIC16F1825
PIC16F1829
Linear Regulator
Power Switch
Push Button
Hello World LED
I2C Pull Up Resistors
PICkit3 Header
PIC Microcontroller
SPI
PWM
UART
ADC
VIVA Headers
Q.sw
Screw Terminal
Transistor Switch
PIC16 Headers

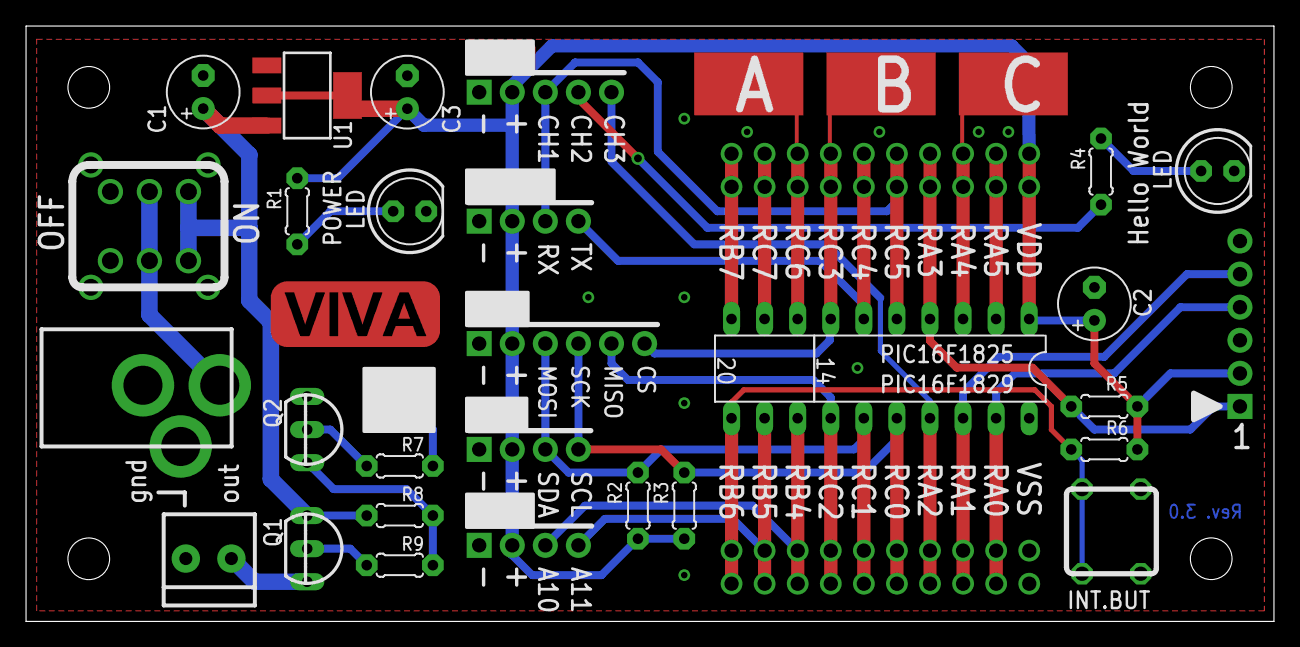
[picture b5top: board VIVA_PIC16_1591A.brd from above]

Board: 2 copper layers, 95.8 x 45.7 mm, 31 parts (0 on the bottom side), 29 nets.

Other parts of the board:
U$2: VIVA_LOGO

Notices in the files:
parts and their libraries:
COPYRIGHT: Copyright (C) 2021 Ultra Librarian. All rights reserved.
